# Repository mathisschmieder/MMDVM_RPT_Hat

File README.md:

# MMDVM_RPT_Hat
MMDVM_RPT_Hat for the Raspberry Pi

This project provides a Raspberry Pi Hat for the [MMDVM](https://github.com/g4klx/MMDVM).

## Revisions

### Revision 0.1
First PCB built for testing purposes.

### Revision 0.2
A second MOSFET transitor has been added to allow for channel switching by the MMDVM.

### Revision 0.3
Another LED was added for the latest implementation of FM mode.

## BOM
* The BOM for the rev0.1 board is available as [Mouser cart](https://www.mouser.com/ProjectManager/ProjectDetail.aspx?AccessID=13f81d64ff).
* [Mouser cart](https://www.mouser.com/ProjectManager/ProjectDetail.aspx?AccessID=fb0666986e) for rev0.2 board.
* Here is the [Mouser cart](https://www.mouser.com/ProjectManager/ProjectDetail.aspx?AccessID=3737004138) for the revision 0.3.

## License
This project is released under the Creative Commons Attribution-NonCommercial-ShareAlike 3.0 (CC-BY-NC-SA 3.0, https://creativecommons.org/licenses/by-nc-sa/3.0/) license. You may edit and share it as you like, as long as credit is given and the license is not changed. You can build as many boards for you and your friends as you like and you can even sell it to them to cover your costs, **however it is strictly forbidden to turn this into a commercial product! You are not allowed to build and sell these boards for profit!**

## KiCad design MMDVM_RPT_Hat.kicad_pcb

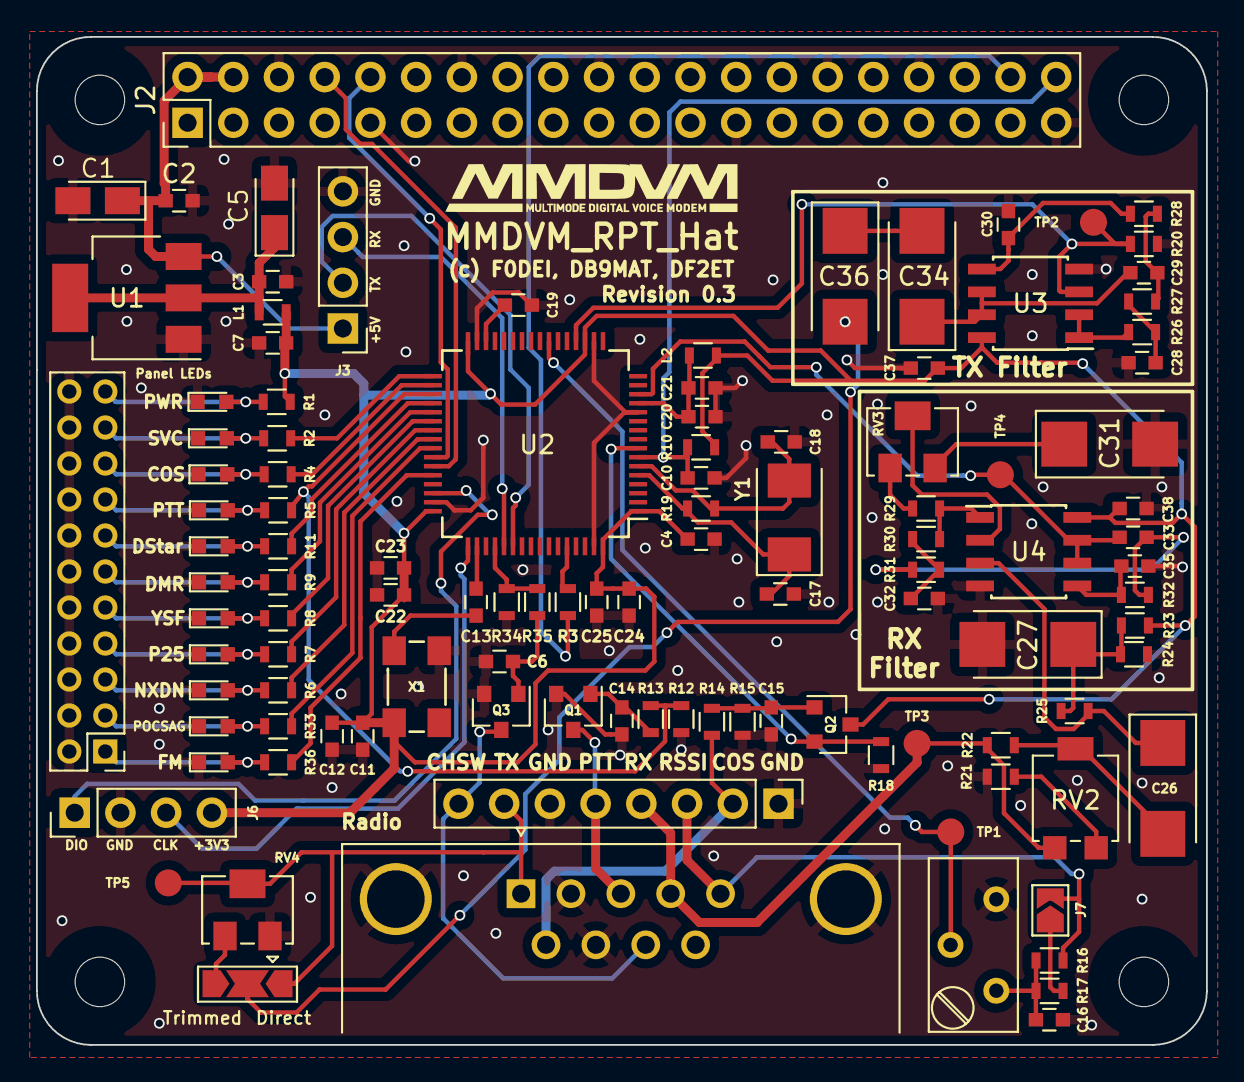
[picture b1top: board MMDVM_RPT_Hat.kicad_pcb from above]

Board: 2 copper layers, 65.0 x 56.0 mm, 111 parts (0 on the bottom side), 75 nets.

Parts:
C1, C5: 10u; CP_Tantalum_Case-A_EIA-3216-18_Reflow
C2, C3, C4, C10, C12, C13, C16, C21, C22, C24, C37, C38: 100n; C_0603
C6, C14, C15: 470p; C_0603
C7: 10u; C_0603
C11, C19, C20, C23, C25: 4u7; C_0603
C17, C18: 20p; C_0603
C26, C27, C31, C34, C36: 47u; CP_Tantalum_Case-C_EIA-6032-28_Reflow
C28, C32: 10n; C_0603
C29, C33: 39n; C_0603
C30, C35: 1n; C_0603
D1: PWR; LED_0603
D2: SVC; LED_0603
D3: COS; LED_0603
D4: PTT; LED_0603
D5: NXDN; LED_0603
D6: P25; LED_0603
D7: YSF; LED_0603
D8: DMR; LED_0603
D9: DSTAR; LED_0603
D10: POCSAG; LED_0603
D11: FM; LED_0603
J1: Radio; DSUB-9_Male_Horizontal_Pitch2.77x2.84mm_EdgePinOffset4.94mm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
J2: Raspberry_Pi_2_3; Pin_Header_Straight_2x20_Pitch2.54mm
J3: Serial Display; Pin_Header_Straight_1x04_Pitch2.54mm
J4: Panel LEDs; PinHeader_2x11_P2.00mm_Vertical
J5: Radio; Pin_Header_Straight_1x08_Pitch2.54mm
J6: STLink; Pin_Header_Straight_1x04_Pitch2.54mm
J7: GS2; SolderJumper-2_P1.3mm_Open_TrianglePad1.0x1.5mm
J8: GS3; SolderJumper-3_P2.0mm_Open_TrianglePad1.0x1.5mm
L1: 10u; L_0603
L2: 600R, 500mA; L_0603
Q1, Q3: IRLML2060; SOT-23
Q2: 2N7002; SOT-23
R1, R2, R4, R5, R6, R7, R8, R9, R11, R33, R36: 1k5; R_0603
R3, R10, R20: 10k; R_0603
R12, R16, R18, R34: 47k; R_0603
R13, R14, R35: 330; R_0603
R15, R19: 1M; R_0603
R17, R27, R28, R31, R32: 4k7; R_0603
R21: 1k; R_0603
R22: 20k; R_0603
R23, R24, R25: 22k; R_0603
R26, R30: 5k1; R_0603
R29: 30k; R_0603
RV1: POT; Potentiometer_Trimmer_Bourns_3296Y
RV2: 10k; Potentiometer_Bourns_3314G_Vertical
RV3: 100k; Potentiometer_Bourns_3214W_Vertical
RV4: 200k; Potentiometer_Bourns_3214W_Vertical
TP1, TP2, TP3, TP4, TP5: TEST; Measurement_Point_Round-SMD-Pad_Small
U1: LD1117S33TR; SOT-223-3_TabPin2
U2: STM32F722RETx; LQFP-64_10x10mm_Pitch0.5mm
U3, U4: MCP6002; SOIC-8_3.9x4.9mm_Pitch1.27mm
X1: TCXO; FOX-924B
Y1: 8 MHz; Crystal_SMD_Abracon_ABM3-2pin_5.0x3.2mm

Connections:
+3V3: C4.2, C7.1, C11.1, C12.1, C22.2, C23.2, C24.2, C25.2, C37.1, C38.1, J6.4, L1.2, L2.1, Q2.3 (D), R1.1, R10.1, R23.1, U2.1 (VBAT), U2.19 (VDD), U2.32 (VDD), U2.48 (VDD), U2.64 (VDD), U3.8 (V+), U4.8 (V+), X1.4 (Vdd)
+5V: C1.1, C2.1, J2.2 (5V), J2.4 (5V), J3.1, U1.3 (VI)
ADC_RX: C33.2, TP4.1, U2.14 (PA0), U4.6 (-), U4.7
BOOT0: R3.2, U2.60 (BOOT0)
CLOCK: C13.1, U2.50 (PA15)
COS: Q2.2 (S), R18.2, U2.8 (PC0)
COS_LED: R4.1, U2.34 (PB13)
DAC_TX: R20.1, TP2.1, U2.20 (PA4), U3.3 (+)
DMR_LED: R9.1, U2.37 (PC6)
DSTAR_LED: R11.1, U2.36 (PB15)
FM_LED: R36.1, U2.44 (PA11)
GND: C1.2, C2.2, C3.2, C4.1, C5.2, C6.2, C7.2, C10.2, C11.2, C12.2, C14.2, C15.2, C16.1, C17.2, C18.2, C19.2, C20.2, C21.2, C22.1, C23.1, C24.1, C25.1, C27.2, C28.2, C30.2, C31.2, C32.2, C35.2, C37.2, C38.2, D1.1 (K), D2.1 (K), D3.1 (K), D4.1 (K), D5.1 (K), D6.1 (K), D7.1 (K), D8.1 (K), D9.1 (K), D10.1 (K), D11.1 (K), J1.0 (PAD), J1.2, J1.7, J2.6 (GND), J2.9 (GND), J2.14 (GND), J2.20 (GND), J2.25 (GND), J2.30 (GND), J2.34 (GND), J2.39 (GND), J3.4, J4.2, J4.4, J4.6, J4.8, J4.10, J4.12, J4.14, J4.16, J4.18, J4.20, J4.22, J5.1, J5.6, J6.2, Q1.2 (S), Q3.2 (S), R12.1, R15.1, R18.1, R20.2, R21.2, R24.1, R34.1, RV1.3, RV4.3, U1.1 (GND), U2.12 (VSSA), U2.18 (VSS), U2.31 (VSS), U2.47 (VSS), U2.63 (VSS), U3.4 (V-), U4.4 (V-), X1.2 (GND)
MPOCSAG: R34.2, R35.2, U2.52 (PC11)
NRST: C10.1, J2.40 (GPIO21), R10.2, U2.7 (NRST)
NXDN_LED: R6.1, U2.40 (PC9)
unnamed: C3.1, C5.1, L1.1, U1.2 (VO)
unnamed: C6.1, Q3.1 (G), R35.1
unnamed: C13.2, X1.3 (OUT)
unnamed: C14.1, Q1.1 (G), R13.1
unnamed: C15.1, Q2.1 (G), R14.1, R15.2
unnamed: C16.2, R16.1, R17.1, RV1.1
unnamed: C17.1, R19.2, U2.5 (PH0), Y1.1
unnamed: C18.1, R19.1, U2.6 (PH1), Y1.2
unnamed: C19.1, U2.30 (VCAP_1)
unnamed: C20.1, C21.1, L2.2, U2.13 (VREF+)
unnamed: C26.1, R25.2, U4.3 (+)
unnamed: C26.2, R22.1, RV2.2
unnamed: C27.1, R23.2, R24.2, R25.1
unnamed: C28.1, R26.1, R27.2
unnamed: C29.1, R27.1, R28.2
unnamed: C29.2, C34.1, U3.6 (-), U3.7
unnamed: C30.1, R28.1, U3.5 (+)
unnamed: C31.1, RV3.3
unnamed: C32.1, R30.1, R31.2
unnamed: C33.1, R31.1, R32.2
unnamed: C34.2, C36.1
unnamed: C35.1, R32.1, U4.5 (+)
unnamed: C36.2, J8.2 (G2)
unnamed: D1.2 (A), J4.21, R1.2
unnamed: D2.2 (A), J4.19, R2.2
unnamed: D3.2 (A), J4.17, R4.2
unnamed: D4.2 (A), J4.15, R5.2
unnamed: D5.2 (A), J4.5, R6.2
unnamed: D6.2 (A), J4.7, R7.2
unnamed: D7.2 (A), J4.9, R8.2
unnamed: D8.2 (A), J4.11, R9.2
unnamed: D9.2 (A), J4.13, R11.2
unnamed: D10.2 (A), J4.3, R33.2
unnamed: D11.2 (A), J4.1, R36.2
unnamed: J2.38 (GPIO20), R3.1
unnamed: J7.1 (G1), R17.2
unnamed: J8.3 (G3), RV4.1
unnamed: R21.1, RV2.3
unnamed: R26.2, U3.1, U3.2 (-)
unnamed: R29.1, R30.2, U4.1
unnamed: R29.2, RV3.1
unnamed: RV3.2, U4.2 (-)
P25_LED: R7.1, U2.39 (PC8)
POCSAG_LED: R33.1, U2.41 (PA8)
PTT: R5.1, R12.2, R13.2, U2.35 (PB14)
RADIO_CH_SW: J1.8, J5.8, Q3.3 (D)
RADIO_COS: J1.6, J5.2, R14.2
RADIO_PTT: J1.3, J5.5, Q1.3 (D)
RADIO_RX: J1.4, J5.4, R22.2, RV2.1, TP3.1
RADIO_TX: J1.1, J5.7, J8.1 (G1), RV4.2, TP5.1
RSSI: RV1.2, TP1.1, U2.23 (PA7)
RX: J2.8 ((TXD0)_GPIO14), U2.43 (PA10)
RX_NEXTION: J3.3, U2.53 (PC12)
R_RSSI: J1.5, J5.3, J7.2 (G2), R16.2
SVC_LED: R2.1, U2.33 (PB12)
SWCLK: J6.3, U2.49 (PA14)
SWDIO: J6.1, U2.46 (PA13)
TX: J2.10 ((RXD0)_GPIO15), U2.42 (PA9)
TX_NEXTION: J3.2, U2.54 (PD2)
YSF_LED: R8.1, U2.38 (PC7)

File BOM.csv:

Refs,Value,Footprint,QTY,MFR,MPN,SPR,SPN
C37;C38;C2;C3;C21;C22;C24;C10;C13;C12;C16;C4,100n,Capacitors_SMD:C_0603,12,KEMET,C0603T104K3RALTU,Mouser,80-C0603T104K3RALTU
C32;C28,10n,Capacitors_SMD:C_0603,2,KEMET,C0603C103K2RECTU,Mouser,80-C0603C103K2REC
C7,10u,Capacitors_SMD:C_0603,1,KEMET,C0603C106M7PACTU,Mouser,80-C0603C106M7P
C35;C30,1n,Capacitors_SMD:C_0603,2,KEMET,C0603S102K4RACTU,Mouser,80-C0603S102K4R
C17;C18,20p,Capacitors_SMD:C_0603,2,KEMET,C0603C200K4GACTU,Mouser,80-C0603C200K4G
C33;C29,39n,Capacitors_SMD:C_0603,2,KEMET,C0603C393K4RACTU,Mouser,80-C0603C393K4R
C14;C15;C6,470p,Capacitors_SMD:C_0603,3,KEMET,C0603C471K4RACTU,Mouser,80-C0603C471K4R
C20;C23;C25;C19;C11,4u7,Capacitors_SMD:C_0603,5,Murata Electronics,GRM188R61C475KAAJD,Mouser,81-GRM188R61C475KAJD
C26;C27;C31;C34;C36,47u,Capacitors_Tantalum_SMD:CP_EIA-6032-28_Kemet-C,5,AVX,TAJC476K016SNJ,Mouser,581-TAJC476K016SNJ
C1;C5,10u,Capacitors_Tantalum_SMD:CP_Tantalum_Case-A_EIA-3216-18_Reflow,2,AVX,F931C106KAA,Mouser,647-F931C106KAA
J7,GS2,Connectors:GS2,1,,,,
J8,GS3,Connectors:GS3,1,,,,
J1,Radio,Connectors_DSub:DSUB-9_Male_Horizontal_Pitch2.77x2.84mm_EdgePinOffset4.94mm_Housed_MountingHolesOffset7.48mm,1,TE Connectivity / AMP,1734354-1,Mouser,571-1734354-1
Y1,8 MHz,Crystals:Crystal_SMD_Abracon_ABM3-2pin_5.0x3.2mm,1,ABRACON,ABM3-8.000MHz-D2Y-T,Mouser,815-ABM3-8-D2Y-T
U2,STM32F722RETx,Housings_QFP:LQFP-64_10x10mm_Pitch0.5mm,1,STMicroelectronics,STM32F722RET6,Mouser,511-STM32F722RET6
U3;U4,MCP6002,Housings_SOIC:SOIC-8_3.9x4.9mm_Pitch1.27mm,2,Microchip Technology,MCP6002-E/SN,Mouser,579-MCP6002-E/SN
L1,10u,Inductors_SMD:L_0603,1,Murata Electronics,LQM18FN100M00D,Mouser,81-LQM18FN100M00D
L2,"600R, 500mA",Inductors_SMD:L_0603,1,Wurth Electronics,742863160,Mouser,710-742863160
D3,COS,LEDs:LED_0603,1,Kingbright,APT1608SYC,Mouser,604-APT1608SYC
D8,DMR,LEDs:LED_0603,1,Kingbright,APT1608SYC,Mouser,604-APT1608SYC
D9,DSTAR,LEDs:LED_0603,1,Kingbright,APT1608SGC,Mouser,604-APT1608SGC
D5,NXDN,LEDs:LED_0603,1,Kingbright,APT1608VBC/D,Mouser,604-APT1608VBC/D
D6,P25,LEDs:LED_0603,1,Kingbright,APT1608SURCK,Mouser,604-APT1608SURCK
D10,POCSAG,LEDs:LED_0603,1,Kingbright,APT1608VBC/D,Mouser,604-APT1608VBC/D
D4,PTT,LEDs:LED_0603,1,Kingbright,APT1608SURCK,Mouser,604-APT1608SURCK
D1,PWR,LEDs:LED_0603,1,Kingbright,APT1608SGC,Mouser,604-APT1608SGC
D2,SVC,LEDs:LED_0603,1,Kingbright,APT1608SURCK,Mouser,604-APT1608SURCK
D7,YSF,LEDs:LED_0603,1,Kingbright,APT1608SECK,Mouser,604-APT1608SECK
D11,FM,LEDs:LED_0603,1,Kingbright,APT1608VBC/D,Mouser,604-APT1608VBC/D
TP3;TP4;TP2;TP5;TP1,TEST,Measurement_Points:Measurement_Point_Round-SMD-Pad_Small,5,,,,
J6,STLink,Pin_Headers:Pin_Header_Straight_1x04_Pitch2.54mm,1,Wurth Electronics,61300411121,Mouser,710-61300411121
J3,Serial Display,Pin_Headers:Pin_Header_Straight_1x04_Pitch2.54mm,1,Wurth Electronics,61300411121,Mouser,710-61300411121
J5,Radio,Pin_Headers:Pin_Header_Straight_1x08_Pitch2.54mm,1,Wurth Electronics,61300811121,Mouser,710-61300811121
J4,Panel LEDs,Connector_PinHeader_2.00mm:PinHeader_2x11_P2.00mm_Vertical,1,Samtec,MTMM-111-09-L-D-380,Mouser,200-MTMM11109LD380
J2,Raspberry_Pi_2_3,Pin_Headers:Pin_Header_Straight_2x20_Pitch2.54mm,1,Harwin,M20-7832046,Mouser,855-M20-7832046
RV3,100k,Potentiometer_SMD:Potentiometer_Bourns_3214W_Vertical,1,Bourns,3214W-1-104E,Mouser,652-3214W-1-104E
RV4,200k,Potentiometer_SMD:Potentiometer_Bourns_3214W_Vertical,1,Bourns,3214W-1-204E,Mouser,652-3214W-1-204E
RV2,10k,Potentiometer_SMD:Potentiometer_Bourns_3314G_Vertical,1,Bourns,3314G-1-103E,Mouser,652-3314G-1-103E
RV1,POT,Potentiometers:Potentiometer_Trimmer_Bourns_3296Y,1,Bourns,3296Y-1-104LF,Mouser,652-3296Y-1-104LF
R20;R3;R10,10k,Resistors_SMD:R_0603,3,Panasonic,ERJ-PB3B1002V,Mouser,667-ERJ-PB3B1002V
R19;R15,1M,Resistors_SMD:R_0603,2,Panasonic,ERJ-3EKF1004V,Mouser,667-ERJ-3EKF1004V
R21,1k,Resistors_SMD:R_0603,1,Panasonic,ERJ-3EKF1001V,Mouser,667-ERJ-3EKF1001V
R1;R2;R4;R5;R6;R7;R8;R9;R11;R33;R36,1k5,Resistors_SMD:R_0603,11,Panasonic,ERJ-3EKF1501V,Mouser,667-ERJ-3EKF1501V
R22,20k,Resistors_SMD:R_0603,1,Panasonic,ERJ-3EKF2002V,Mouser,667-ERJ-3EKF2002V
R25;R23;R24,22k,Resistors_SMD:R_0603,3,Panasonic,ERJ-P03F2202V,Mouser,667-ERJ-P03F2202V
R29,30k,Resistors_SMD:R_0603,1,Panasonic,ERJ-3EKF3002V,Mouser,667-ERJ-3EKF3002V
R13;R14;R35,330,Resistors_SMD:R_0603,3,Panasonic,ERJ-U03F3300V,Mouser,667-ERJ-U03F3300V
R16;R12;R18;R34,47k,Resistors_SMD:R_0603,4,Panasonic,ERJ-3EKF4702V,Mouser,667-ERJ-3EKF4702V
R31;R32;R27;R28;R17,4k7,Resistors_SMD:R_0603,5,Panasonic,ERJ-3EKF4701V,Mouser,667-ERJ-3EKF4701V
R30;R26,5k1,Resistors_SMD:R_0603,2,Panasonic,ERJ-3EKF5101V,Mouser,667-ERJ-3EKF5101V
U1,LD1117S33TR,TO_SOT_Packages_SMD:SOT-223-3_TabPin2,1,STMicroelectronics,LD1117S33TR,Mouser,511-LD1117S33
Q2,2N7002,TO_SOT_Packages_SMD:SOT-23,1,ON Semiconductor / Fairchild,2N7002,Mouser,512-2N7002
Q1;Q3,IRLML2060,TO_SOT_Packages_SMD:SOT-23,2,Infineon Technologies,IRLML2060TRPBF,Mouser,942-IRLML2060TRPBF
X1,TCXO,lib:FOX-924B,1,Fox,FOX924B-12,Mouser,559-FOX924B-12

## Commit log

2018-06-26 Revision 0.1
2018-06-29 Add value for R19 and BOM
2018-06-29 Correct part for 10nF capacitors
2018-06-29 Add README
2018-06-30 Change Case code for 47u caps
2018-06-30 Remof00
2018-07-23 Re-add lost C4
2018-07-24 Add Channel switch line (schematic only)
2018-07-24 Use FET for channel switch
2018-07-24 Update netlist
2018-07-24 Revision 0.2: Added FET for channel switching; Rename to MMDVM_RPT_Hat
2018-07-24 Aligned radio connector
2018-07-24 Added more GND vias
2018-07-24 Rename files to MMDVM_RPT_Hat
2018-07-24 Rename CH_SW to MPOCSAG
2020-05-11 Re-add OSHW and KiCad logos as well as drill file
2020-05-11 Add drill file
2020-05-12 Forgot to include the Mask layer in gerbers ... :/
2020-09-28 Fixed README for Github
